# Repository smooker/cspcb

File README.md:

# stepper_sc — STM32F411 Stepper Controller PCB

Single-axis stepper motor controller board built around the **WeAct STM32F411CEU6 Black Pill v3.1**.

Drives a **CWD556** opto-isolated stepper driver (PUL/DIR interface) from MCU outputs via NPN buffer stage.

## Block Diagram

```
24V ──── 78M05 ──── +5V ──── Black Pill (3.3V regulator on-board)
                              │
                    PB10 ─── R1/R2/Q1 ─── J2 (PUL → CWD556)
                    PB14 ─── R3/R4/Q2 ─── J3 (DIR → CWD556)
                    PA3  ─── J4 (Endstop L)
                    PA4  ─── J5 (Endstop R)
                    PA6  ─── J6 (Jog L)
                    PA7  ─── J7 (Jog R)
                    PB0  ─── J8 (Step L)
                    PB1  ─── J9 (Step R)
                    PB15 ─── J10 (Buzzer)
```

## Hardware

| Ref | Value | Function |
|-----|-------|----------|
| U1 | 78M05 | 24V → 5V regulator |
| Q1, Q2 | BC547 | NPN buffer (PUL, DIR) |
| R1, R3 | 1kΩ | Base resistor |
| R2, R4 | 10kΩ | Base pull-down |
| C1 | 47µF | Regulator input bulk |
| C2, C4 | 100nF | Regulator decoupling |
| C3 | 100µF | Regulator output bulk |
| C5 | 100nF | Black Pill VIN decoupling |
| J1 | 2-pin screw | 24V power input |
| J2 | 2-pin screw | PUL output to CWD556 |
| J3 | 2-pin screw | DIR output to CWD556 |
| J4–J10 | 2-pin screw | Signal terminals |
| J11A, J11B | 1×20 header | Black Pill socket |

## Pipeline

Schematic and netlist are **generated from firmware source** — `main.h` is the single source of truth for MCU pin assignments.

```
firmware/Core/Inc/main.h
        │
        ▼ fw_to_net.py
howto_sch_and_then_api/stepper_sc.net
        │
        ▼ howto_sch_and_then_api/stepper_sc_gen.py
stepper_sc/stepper_sc.kicad_sch
```

### Re-generating after pin changes

```bash
# Activate venv (needs kicad-sch-api)
source venv/bin/activate

# Step 1: netlist from firmware
python3 fw_to_net.py

# Step 2: schematic from netlist
python3 howto_sch_and_then_api/stepper_sc_gen.py
```

### Setup

```bash
python3 -m venv venv
venv/bin/pip install kicad-sch-api

# KiCad symbol libraries — set path to your KiCad install
# e.g. /usr/share/kicad/symbols
ln -s /path/to/kicad/symbols kicad_sym
```

## Firmware

See `firmware/` for STM32 application source (`Core/`).

Requires ST HAL (`Drivers/`) — generate via STM32CubeMX or download from [st.com](https://www.st.com).

Build:
```bash
cd firmware && make
```

Flash via Black Magic Probe:
```bash
arm-none-eabi-gdb -x script2.gdb build/stepper.elf
```

See `doc/build-and-debug.md` for full build, flash and debug instructions.

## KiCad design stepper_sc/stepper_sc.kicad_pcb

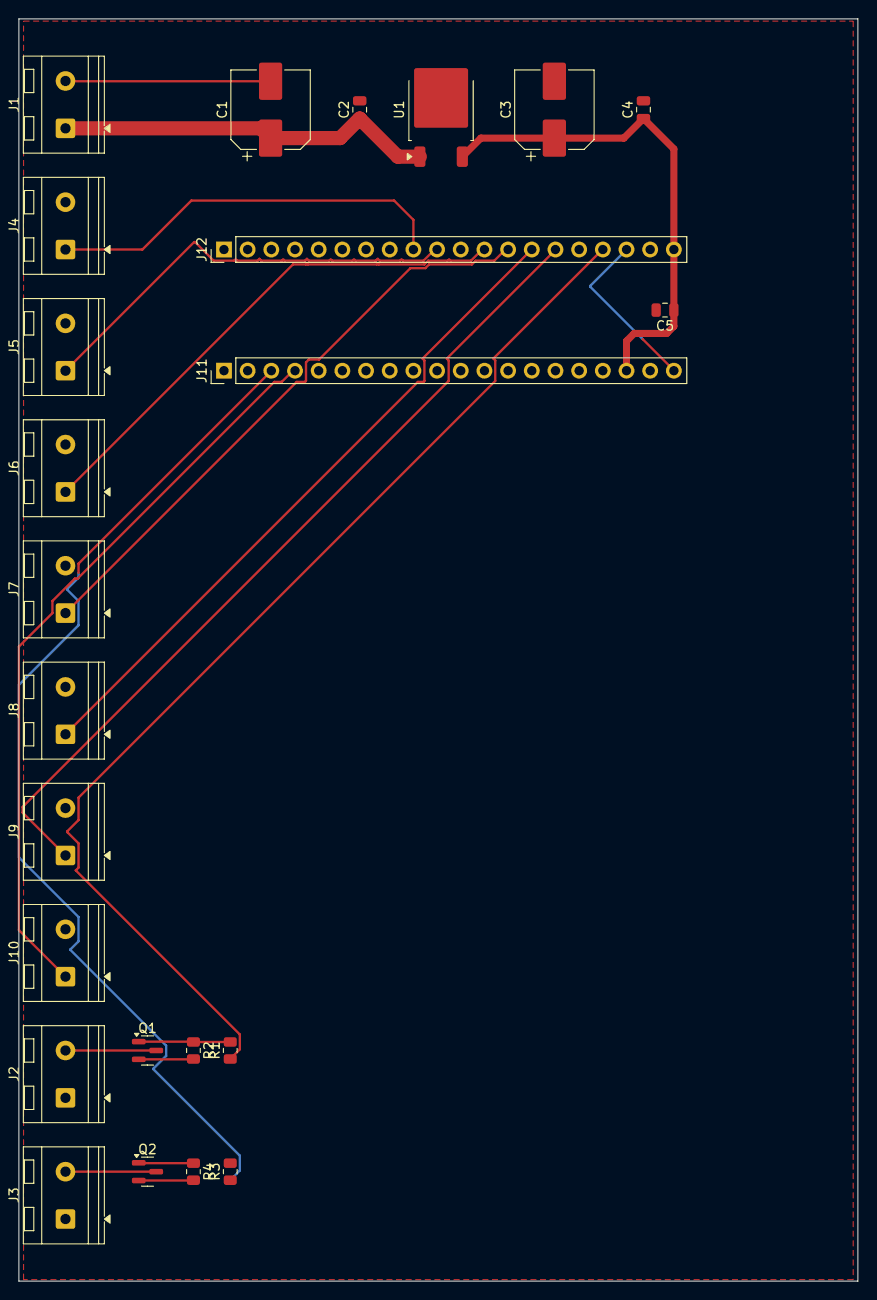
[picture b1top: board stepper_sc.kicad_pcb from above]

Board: 2 copper layers, 90.0 x 135.4 mm, 24 parts (0 on the bottom side), 17 nets.

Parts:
C1: 47uF; CP_Elec_8x6.2
C2, C4, C5: 100nF; C_0805_2012Metric
C3: 100uF; CP_Elec_8x6.2
J1: PWR_24V; TerminalBlock_RND_205-00232_1x02_P5.08mm_Horizontal
J2: PUL; TerminalBlock_RND_205-00232_1x02_P5.08mm_Horizontal
J3: DIR; TerminalBlock_RND_205-00232_1x02_P5.08mm_Horizontal
J4: ES_L; TerminalBlock_RND_205-00232_1x02_P5.08mm_Horizontal
J5: ES_R; TerminalBlock_RND_205-00232_1x02_P5.08mm_Horizontal
J6: JOGL; TerminalBlock_RND_205-00232_1x02_P5.08mm_Horizontal
J7: JOGR; TerminalBlock_RND_205-00232_1x02_P5.08mm_Horizontal
J8: STEPL; TerminalBlock_RND_205-00232_1x02_P5.08mm_Horizontal
J9: STEPR; TerminalBlock_RND_205-00232_1x02_P5.08mm_Horizontal
J10: BUZZ; TerminalBlock_RND_205-00232_1x02_P5.08mm_Horizontal
J11: Black_Pill_front; PinHeader_1x20_P2.54mm_Vertical
J12: Black_Pill_back; PinHeader_1x20_P2.54mm_Vertical
Q1, Q2: BC547; SOT-23
R1, R3: 1k; R_0805_2012Metric
R2, R4: 10k; R_0805_2012Metric
U1: 78M05; TO-252-2

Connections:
+3.3V: J11.20, J12.18
+5V: C3.1, C4.1, C5.1, J2.1, J3.1, J11.18, J12.20, U1.3
+24V: C1.1, C2.1, J1.1, U1.1
GND: C1.2, C2.2, C3.2, C4.2, C5.2, J1.2, J4.2, J5.2, J6.2, J7.2, J8.2, J9.2, J10.2, J11.19, J12.19, Q1.2, Q2.2, R2.2, R4.2, U1.2
unnamed: J2.2, Q1.3
unnamed: J3.2, Q2.3
unnamed: J10.1, J11.4
unnamed: J11.3, R3.1
unnamed: J4.1, J12.9
unnamed: J5.1, J12.10
unnamed: J6.1, J12.12
unnamed: J7.1, J12.13
unnamed: J8.1, J12.14
unnamed: J9.1, J12.15
unnamed: J12.17, R1.1
unnamed: Q1.1, R1.2, R2.1
unnamed: Q2.1, R3.2, R4.1

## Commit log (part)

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2026-03-12 pushed from sw2
